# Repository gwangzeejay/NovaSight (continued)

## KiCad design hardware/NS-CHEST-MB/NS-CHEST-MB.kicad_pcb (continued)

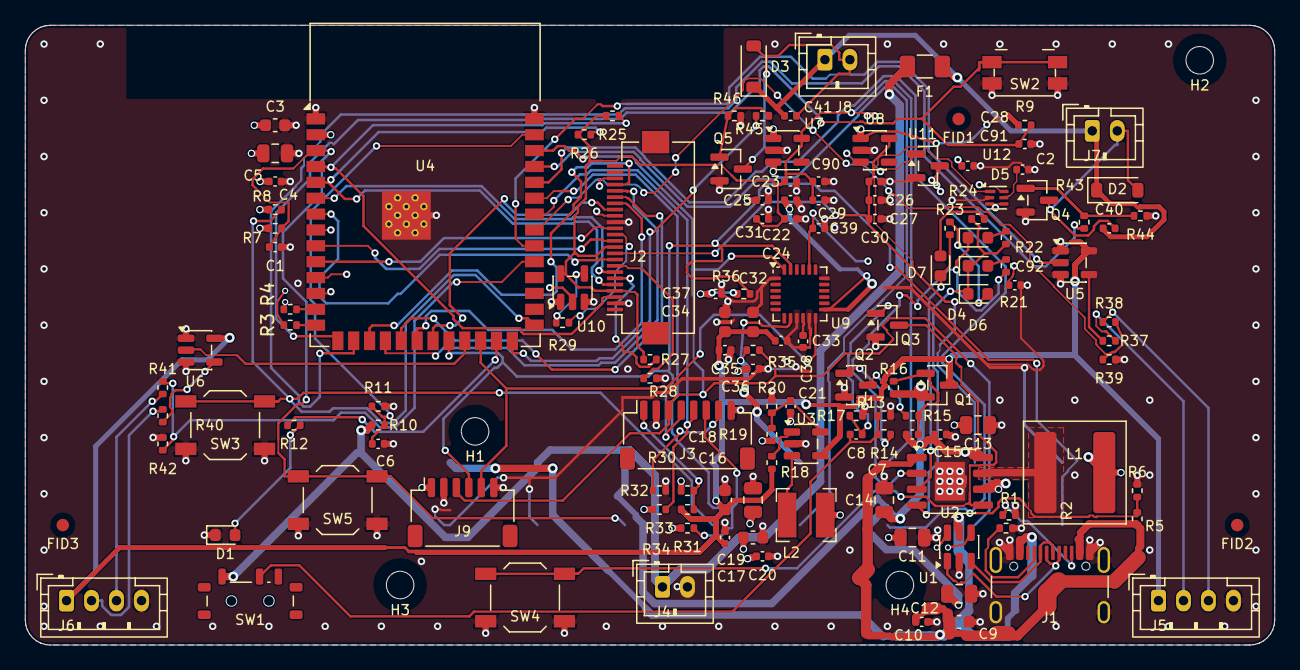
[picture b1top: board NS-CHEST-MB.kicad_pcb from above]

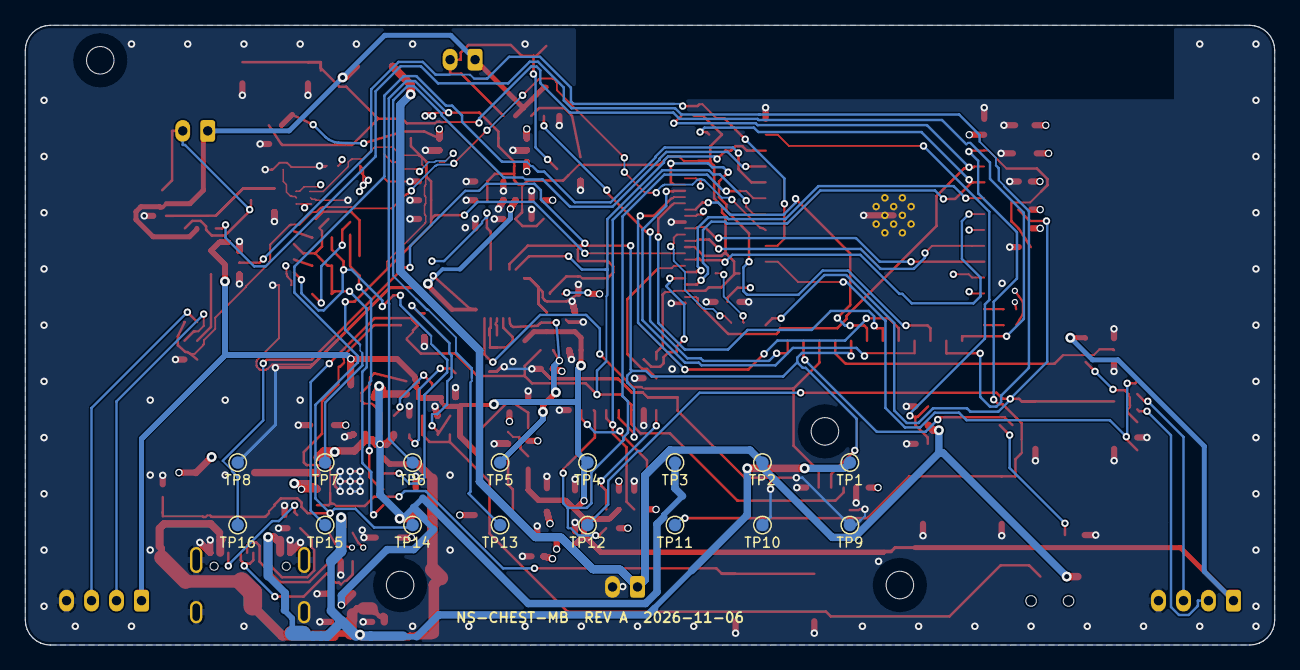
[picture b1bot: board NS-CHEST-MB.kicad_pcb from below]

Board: 4 copper layers, 100.0 x 49.6 mm, 154 parts (16 on the bottom side), 87 nets.

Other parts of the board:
FID1, FID2, FID3: FIDUCIAL; Fiducial_1mm_Mask2mm
H1, H2, H3, H4: M2_NPTH; MountingHole_2.2mm_M2

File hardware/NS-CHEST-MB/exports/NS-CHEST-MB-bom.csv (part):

"Refs","Value","Footprint","Qty","DNP"
"C1","1uF_10V","Capacitor_SMD:C_0402_1005Metric","1",""
"C2","100nF_10V","Capacitor_SMD:C_0402_1005Metric","1",""
"C3","10uF_10V","Capacitor_SMD:C_0603_1608Metric","1",""
"C4","100nF_10V","Capacitor_SMD:C_0402_1005Metric","1",""
"C5","22uF_10V","Capacitor_SMD:C_0805_2012Metric","1",""
"C6","100nF_10V","Capacitor_SMD:C_0402_1005Metric","1",""
"C7","100nF_10V","Capacitor_SMD:C_0402_1005Metric","1",""
"C8","1uF_10V","Capacitor_SMD:C_0402_1005Metric","1",""
"C9","10uF_10V","Capacitor_SMD:C_0603_1608Metric","1",""
"C10","100nF_10V","Capacitor_SMD:C_0402_1005Metric","1",""
"C11","22uF_10V","Capacitor_SMD:C_0805_2012Metric","1",""
"C12","22uF_10V","Capacitor_SMD:C_0805_2012Metric","1",""
"C13","22uF_10V","Capacitor_SMD:C_0805_2012Metric","1",""
"C14","22uF_10V","Capacitor_SMD:C_0805_2012Metric","1",""
"C15","100nF_10V","Capacitor_SMD:C_0402_1005Metric","1",""
"C16","10uF_10V","Capacitor_SMD:C_0603_1608Metric","1",""
"C17","100nF_10V","Capacitor_SMD:C_0402_1005Metric","1",""
"C18","22uF_10V","Capacitor_SMD:C_0805_2012Metric","1",""
"C19","10uF_10V","Capacitor_SMD:C_0603_1608Metric","1",""
"C20","100nF_10V","Capacitor_SMD:C_0402_1005Metric","1",""
"C21","22pF_50V","Capacitor_SMD:C_0402_1005Metric","1",""
"C22","1uF_10V","Capacitor_SMD:C_0402_1005Metric","1",""
"C23","1uF_10V","Capacitor_SMD:C_0402_1005Metric","1",""
"C24","100nF_10V","Capacitor_SMD:C_0402_1005Metric","1",""
"C25","1uF_10V","Capacitor_SMD:C_0402_1005Metric","1",""
"C26","1uF_10V","Capacitor_SMD:C_0402_1005Metric","1",""
"C27","100nF_10V","Capacitor_SMD:C_0402_1005Metric","1",""
"C28","100nF_10V","Capacitor_SMD:C_0402_1005Metric","1",""
"C29","1uF_10V","Capacitor_SMD:C_0402_1005Metric","1",""
"C30","1uF_10V","Capacitor_SMD:C_0402_1005Metric","1",""
"C31","1uF_10V","Capacitor_SMD:C_0402_1005Metric","1",""
"C32","10uF_10V","Capacitor_SMD:C_0603_1608Metric","1",""
"C33","100nF_10V","Capacitor_SMD:C_0402_1005Metric","1",""
"C34","10uF_10V","Capacitor_SMD:C_0603_1608Metric","1",""
"C35","100nF_10V","Capacitor_SMD:C_0402_1005Metric","1",""
"C36","100nF_10V","Capacitor_SMD:C_0402_1005Metric","1",""
"C37","10nF_10V","Capacitor_SMD:C_0402_1005Metric","1",""
"C38","100nF_10V","Capacitor_SMD:C_0402_1005Metric","1",""
"C39","2.2nF_50V","Capacitor_SMD:C_0402_1005Metric","1",""
"C40","100nF_10V","Capacitor_SMD:C_0402_1005Metric","1",""
"C41","100nF_10V","Capacitor_SMD:C_0402_1005Metric","1",""
"C90","100nF_10V","Capacitor_SMD:C_0402_1005Metric","1",""
"D1","STATUS_WHITE","LED_SMD:LED_0603_1608Metric","1",""
"D2","B5819W","Diode_SMD:D_SOD-123","1",""
"D3","B5819W","Diode_SMD:D_SOD-123","1",""
"D4","SOC_GREEN","LED_SMD:LED_0603_1608Metric","1",""
"D5","SOC_GREEN","LED_SMD:LED_0603_1608Metric","1",""
"D6","SOC_GREEN","LED_SMD:LED_0603_1608Metric","1",""
"D7","SOC_GREEN","LED_SMD:LED_0603_1608Metric","1",""
"F1","PTC_HOLD_0.5A","Fuse:Fuse_1206_3216Metric","1",""
"J1","USB-C","Connector_USB:USB_C_Receptacle_GCT_USB4105-xx-A_16P_TopMnt_Horizontal","1",""
"J2","OV5640_FPC_VERIFY_CONTACT","Connector_FFC-FPC:Hirose_FH12-24S-0.5SH_1x24-1MP_P0.50mm_Horizontal","1",""
"J3","TOF_HARNESS_VERIFY","Connector_JST:JST_SH_SM08B-SRSS-TB_1x08-1MP_P1.00mm_Horizontal","1",""
"J4","BATTERY_PROTECTED_1S","Connector_JST:JST_PH_B2B-PH-K_1x02_P2.00mm_Vertical","1",""
"J5","JSN_R_VERIFY","Connector_JST:JST_PH_B4B-PH-K_1x04_P2.00mm_Vertical","1",""
"J6","JSN_L_VERIFY","Connector_JST:JST_PH_B4B-PH-K_1x04_P2.00mm_Vertical","1",""
"J7","MOTOR_R","Connector_JST:JST_PH_B2B-PH-K_1x02_P2.00mm_Vertical","1",""
"J8","MOTOR_L","Connector_JST:JST_PH_B2B-PH-K_1x02_P2.00mm_Vertical","1",""
"J9","GY521_OPTION_DNP","Connector_JST:JST_SH_SM06B-SRSS-TB_1x06-1MP_P1.00mm_Horizontal","1","DNP"
"L1","XAL7020-102_1uH_VERIFY","Inductor_SMD:L_Coilcraft_XAL7020-102","1",""
"L2","2.2uH_Isat1.5A","Inductor_SMD:L_Bourns-SRN4018","1",""
"Q1","AO3401A","Package_TO_SOT_SMD:SOT-23","1",""
"Q2","AO3400A","Package_TO_SOT_SMD:SOT-23","1",""
"Q3","2N7002","Package_TO_SOT_SMD:SOT-23","1",""
"Q4","AO3400A","Package_TO_SOT_SMD:SOT-23","1",""
"Q5","AO3400A","Package_TO_SOT_SMD:SOT-23","1",""
"R1","5.1k_1%","Resistor_SMD:R_0402_1005Metric","1",""
"R2","5.1k_1%","Resistor_SMD:R_0402_1005Metric","1",""
"R3","0R","Resistor_SMD:R_0402_1005Metric","1",""
"R4","0R","Resistor_SMD:R_0402_1005Metric","1",""
"R5","68k_1%","Resistor_SMD:R_0402_1005Metric","1",""
"R6","100k_1%","Resistor_SMD:R_0402_1005Metric","1",""
"R7","10k","Resistor_SMD:R_0402_1005Metric","1",""
"R8","10k","Resistor_SMD:R_0402_1005Metric","1",""
"R9","10k","Resistor_SMD:R_0402_1005Metric","1",""
"R10","470k_1%","Resistor_SMD:R_0402_1005Metric","1",""
"R11","470k_1%","Resistor_SMD:R_0402_1005Metric","1",""
"R12","1k","Resistor_SMD:R_0402_1005Metric","1",""
"R13","100k","Resistor_SMD:R_0402_1005Metric","1",""
"R14","10k","Resistor_SMD:R_0402_1005Metric","1",""
"R15","10k","Resistor_SMD:R_0402_1005Metric","1",""
"R16","100k","Resistor_SMD:R_0402_1005Metric","1",""
"R17","470k","Resistor_SMD:R_0402_1005Metric","1",""
"R18","100k","Resistor_SMD:R_0402_1005Metric","1",""
"R19","680k_1%","Resistor_SMD:R_0402_1005Metric","1",""
"R20","150k_1%","Resistor_SMD:R_0402_1005Metric","1",""
"R21","1k","Resistor_SMD:R_0402_1005Metric","1",""
"R22","1k","Resistor_SMD:R_0402_1005Metric","1",""
"R23","1k","Resistor_SMD:R_0402_1005Metric","1",""
"R24","1k","Resistor_SMD:R_0402_1005Metric","1",""
"R25","4.7k","Resistor_SMD:R_0402_1005Metric","1",""
"R26","4.7k","Resistor_SMD:R_0402_1005Metric","1",""
"R27","10k","Resistor_SMD:R_0402_1005Metric","1",""
"R28","10k","Resistor_SMD:R_0402_1005Metric","1",""
"R29","22R","Resistor_SMD:R_0402_1005Metric","1",""
"R30","0R","Resistor_SMD:R_0402_1005Metric","1",""
"R31","0R_OPTION_5V","Resistor_SMD:R_0402_1005Metric","1","DNP"
"R32","0R","Resistor_SMD:R_0402_1005Metric","1",""
"R33","47k","Resistor_SMD:R_0402_1005Metric","1",""
"R34","47k","Resistor_SMD:R_0402_1005Metric","1","DNP"
"R35","2.2k","Resistor_SMD:R_0402_1005Metric","1",""
"R36","2.2k","Resistor_SMD:R_0402_1005Metric","1",""
"R37","100R","Resistor_SMD:R_0402_1005Metric","1",""
"R38","10k_1%","Resistor_SMD:R_0402_1005Metric","1",""
"R39","15k_1%","Resistor_SMD:R_0402_1005Metric","1",""
"R40","100R","Resistor_SMD:R_0402_1005Metric","1",""
"R41","10k_1%","Resistor_SMD:R_0402_1005Metric","1",""
"R42","15k_1%","Resistor_SMD:R_0402_1005Metric","1",""
"R43","100R","Resistor_SMD:R_0402_1005Metric","1",""
"R44","100k","Resistor_SMD:R_0402_1005Metric","1",""
"R45","100R","Resistor_SMD:R_0402_1005Metric","1",""
"R46","100k","Resistor_SMD:R_0402_1005Metric","1",""
"SW1","POWER_ON","Button_Switch_SMD:SW_SPDT_Shouhan_MSK12C02","1",""
"SW2","MODE_EVQPUJ02K_SIDE","Button_Switch_SMD:Panasonic_EVQPUJ_EVQPUA","1",""
"SW3","BOOT","Button_Switch_SMD:SW_SPST_TL3342","1",""
"SW4","IP_KEY_TEST","Button_Switch_SMD:SW_SPST_TL3342","1","DNP"
"SW5","RESET","Button_Switch_SMD:SW_SPST_TL3342","1",""
"TP1","VBUS","TestPoint:TestPoint_Pad_D1.0mm","1",""
"TP2","VBAT","TestPoint:TestPoint_Pad_D1.0mm","1",""
"TP3","5V_SYS","TestPoint:TestPoint_Pad_D1.0mm","1",""
"TP4","5V_SW","TestPoint:TestPoint_Pad_D1.0mm","1",""
"TP5","3V3","TestPoint:TestPoint_Pad_D1.0mm","1",""
"TP6","2V8","TestPoint:TestPoint_Pad_D1.0mm","1",""
"TP7","1V5","TestPoint:TestPoint_Pad_D1.0mm","1",""
"TP8","GND","TestPoint:TestPoint_Pad_D1.0mm","1",""
"TP9","GND","TestPoint:TestPoint_Pad_D1.0mm","1",""
"TP10","GND","TestPoint:TestPoint_Pad_D1.0mm","1",""
"TP11","MCU_EN","TestPoint:TestPoint_Pad_D1.0mm","1",""
"TP12","BOOT","TestPoint:TestPoint_Pad_D1.0mm","1",""
"TP13","UART_TX","TestPoint:TestPoint_Pad_D1.0mm","1",""
"TP14","VBUS_DET","TestPoint:TestPoint_Pad_D1.0mm","1",""
"TP15","I2C_SDA","TestPoint:TestPoint_Pad_D1.0mm","1",""
"TP16","I2C_SCL","TestPoint:TestPoint_Pad_D1.0mm","1",""
"U1","USBLC6-2SC6","Package_TO_SOT_SMD:SOT-23-6","1",""
"U2","IP5306","Package_SO:HSOP-8-1EP_3.9x4.9mm_P1.27mm_EP2.41x3.1mm","1",""
"U3","SY8088IAAC","Package_TO_SOT_SMD:SOT-23-5","1",""
"U4","ESP32-S3-WROOM-1-N16R8","RF_Module:ESP32-S3-WROOM-1","1",""
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
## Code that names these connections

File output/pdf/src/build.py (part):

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    boxes = {'usb': (0, 0, 'J1 USB-C', 'VBUS 4,65–5,5 V', True), 'ip': (1, 0, 'U2 IP5306', 'Sạc 2,1 A + boost 5 V', False),
             'q1': (2, 0, 'Q1 AO3401A', 'Công tắc tải 5V_SYS → 5V_SW', False), 'buck': (3, 0, 'U3 SY8088IAAC', 'Buck 3,3 V, tối đa 1 A', False),
             'v33': (4, 0, '3V3', 'ESP32-S3, MPU-6050, ToF', True),
             'bat': (1, 1, 'J4 pin LP124065', 'VBAT 3,0–4,2 V (có mạch bảo vệ)', True), 'sw': (2, 1, 'SW1 → Q2', 'PWR_EN kéo gate Q1 xuống', False),
             'jsn': (3, 1, 'U5, U6 + J5, J6', '5V_SW: 2 JSN-SR04T, buffer TRIG', False), 'ldo': (4, 1, 'U7 2V8 · U8 1V5', 'Camera AVDD/DOVDD · DVDD', False),
             'f1': (1, 2, 'F1 PTC 0,5 A', 'VBAT → VBAT_MOT', False), 'mot': (2, 2, 'Q4, Q5 + J7, J8', 'Low-side AO3400A, 2 motor 1027', False)}
    arrows = [('line', 'usb', 'r', 'ip', 'l'), ('line', 'ip', 'r', 'q1', 'l'), ('line', 'q1', 'r', 'buck', 'l'), ('line', 'buck', 'r', 'v33', 'l'),
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    # elbow from battery bottom down to Q2 right side: custom since it leaves from bottom
    arrows = [a for a in arrows if a[0] != 'elbow']
    _tree('NovaCane Clip Cây nguồn', 'Mạch chia tải cho phép máy chạy khi cắm sạc; motor lấy nguồn từ VSYS.', boxes, arrows,
          'Khi có VBUS, gate Q2 lên 5 V nên Q2 ngắt; VSYS lấy từ USB qua D4 và TP4056 sạc pin đúng dòng đặt. GND trên bo là P− của mạch bảo vệ; B− không được nối GND ở chỗ khác.')
    # pin → Q2 (battery bottom to Q2 right)
    bxp = 64 + 3 * 238 + 95; yq = H - 135 - 118 - 35
    c.setStrokeColor(GRAY); c.setLineWidth(1.2); c.line(bxp, H - 135 - 70, bxp, yq)
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def block_chest():
    doc.std('NovaChest Kiến trúc phần cứng', 'Mọi GPIO của ESP32-S3 đã được dùng hết; GPIO35–37 bị PSRAM octal chiếm.', 1)
    cx, cy, cw, chh = 400, H - 130, 280, 330
    doc.box(cx, cy, cw, chh, 'U4 ESP32-S3-WROOM-1-N16R8', 'Wi-Fi/BLE 5, 16 MB flash, 8 MB PSRAM\nI²C 400 kHz (GPIO2/14)\nUSB nội GPIO19/20', fill=HEAD, stroke=RED, tsize=15, bsize=12)
    L = [('J1 USB-C + U1 USBLC6', 'CC 5,1 kΩ ×2, D+/D−, VBUS_DET GPIO44'), ('SW2 Mode · SW3 BOOT · SW5 RESET', 'GPIO3, GPIO0, EN'),
         ('U9 MPU-6050', 'I²C 0x68, INT GPIO47'), ('J3 ToF VL53L8CX', 'I²C 0x29, LPn GPIO41, INT GPIO42'), ('Đo pin', 'VBAT/2 → GPIO1 (ADC1_CH0)')]
    R = [('J2 camera FPC 24 chân', 'DVP 8 bit, SCCB GPIO4/5, XCLK GPIO15'), ('U5, U6 → J5, J6 JSN-SR04T', 'TRIG GPIO21/39, ECHO GPIO38/40'),
         ('Q4, Q5 → J7, J8 motor', 'PWM GPIO45/46, kéo xuống 100 kΩ'), ('D1 LED trạng thái', 'GPIO48'), ('TP1–TP16', 'Test point các rail và tín hiệu')]
    for i, (t, b) in enumerate(L):
        yt = H - 125 - i * 66
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
def block_clip():
    doc.std('NovaCane Clip Kiến trúc phần cứng', 'ESP32-C3-MINI-1: một cổng USB-Serial-JTAG dùng cho cả sạc và nạp firmware.', 1)
    doc.box(400, H - 130, 280, 330, 'U1 ESP32-C3-MINI-1-N4X', 'BLE 5, I²C GPIO4/5\nUSB D− GPIO18, D+ GPIO19\nBOOT GPIO9, strapping GPIO2/8/9', fill=HEAD, stroke=RED, tsize=15, bsize=12)
    L = [('J1 USB-C + U2 USBLC6', 'VBUS_DET GPIO21 (cầu chia 68 kΩ / 100 kΩ)'), ('SW2 Mode · SW3 Xin đường · SW4 SOS', 'GPIO10, GPIO2, GPIO20'),
         ('U6 MPU-6050', 'I²C 0x68, INT GPIO1'), ('Đo pin', 'BAT+/2 → GPIO0 (ADC1_CH0)'), ('SW1 công tắc gạt', 'EN của U4 (LDO) nối VSYS khi ON')]
    R = [('Q3, Q4 → motor trái/phải', 'PWM GPIO6/7, VSYS, flyback B5819W'), ('Q5 → D1, D2, D3', 'GPIO3, 2 Hz, 3 nhánh có điện trở riêng'),
         ('D9 LED trạng thái', 'GPIO8, sáng khi mức thấp'), ('D7, D8 CHRG/STDBY', 'Chỉ để kỹ thuật viên xem khi mở vỏ'), ('TP1–TP13', 'Test point các rail và tín hiệu')]
    for i, (t, b) in enumerate(L):
        yt = H - 125 - i * 66
        doc.box(64, yt, 280, 56, t, b, tsize=13, bsize=11); doc.arrow(344, yt - 28, 400, yt - 28)
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rows = [['Khối', 'Linh kiện', 'Hoạt động'],
        ['Sạc', 'U3 TP4056 (ESOP-8), R_PROG 3,0 kΩ', 'I = 1200 / 3,0 = 400 mA; TEMP nối GND; CE nối VCC; pad đáy nối GND'],
        ['Bảo vệ pin', 'U5 DW01A + Q1 FS8205A', '100 Ω từ B+ vào VCC, 100 nF VCC–B−, 1 kΩ từ CS đến P−; FS8205A nằm trên đường B− → P−'],
        ['Chia tải', 'D4 SS14 + Q2 AO3401A', 'Không cắm sạc: gate = 0 V, Q2 dẫn, pin cấp VSYS. Cắm sạc: gate = 5 V, Q2 ngắt, VSYS lấy từ USB qua D4'],
        ['LDO', 'U4 AP2112K-3.3', 'VIN = VSYS; EN nối VSYS qua SW1; ra 10 µF + 100 nF, thêm 22 µF sát chân 3V3 của module'],
        ['Công tắc', 'SW1', 'Chỉ mang dòng µA; OFF thì LDO tắt, dòng còn lại ≈ 4,5 µA cầu chia pin + dòng nghỉ DW01A']]
y_cs = doc.table(64, H - 115, [130, 270, 536], rows, size=15, pad=6.5)
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
S = lambda x0, y0, x1, y1: (x0 / 2000, y0 / 1413, x1 / 2000, y1 / 1413)
sch_page('NovaChest schematic MCU, boot và giao diện', 'Phần 1: ESP32-S3, EN/BOOT, nút Mode, LED trạng thái và đo pin.', 'CH', S(29, 80, 665, 560),
         'U4 ESP32-S3-WROOM-1-N16R8.\nEN: 10 kΩ lên 3V3, 1 µF xuống GND, nút RESET (SW5).\nGPIO0: 10 kΩ lên 3V3, nút BOOT (SW3).\nSW2 Mode: GPIO3, 10 kΩ lên 3V3, 100 nF.\nD1 LED trạng thái: GPIO48 → 1 kΩ.\nĐo pin: VBAT → 470 kΩ / 470 kΩ → GPIO1, 100 nF.')
sch_page('NovaChest schematic nguồn, sạc và bảo vệ', 'Phần 2: IP5306, công tắc tải Q1/Q2/Q3, buck SY8088 và 4 LED báo pin.', 'CH', S(670, 100, 1440, 600),
         'U2 IP5306: VIN = VBUS, BAT = VBAT, SW → L1 → BAT, VOUT = 5V_SYS.\nQ1 AO3401A là công tắc tải 5V_SYS → 5V_SW; Q2 AO3400A và Q3 2N7002 tạo xung KEY.\nU3 SY8088IAAC: R trên 680 kΩ, R dưới 150 kΩ, feed-forward 22 pF cho 3,32 V.\nD4–D7 là mạch báo pin 4 LED.')
sch_page('NovaChest schematic USB-C, ESD và VBUS', 'Phần 3: J1 USB-C, USBLC6-2SC6, CC1/CC2 và cầu chia VBUS_DET.', 'CH', S(29, 590, 665, 1010),
         'CC1 và CC2 mỗi chân một điện trở 5,1 kΩ 1% xuống GND (thiết bị sink).\nD+ nối GPIO20, D− nối GPIO19, có footprint 0 Ω nối tiếp.\nU1 USBLC6-2SC6 bảo vệ D+/D− và VBUS.\nVBUS → 68 kΩ / 100 kΩ → GPIO44 (VBUS_DET), 2,98 V ở 5,0 V.')
sch_page('NovaChest schematic IMU, I²C và cảm biến ngoài', 'Phần 4: MPU-6050, connector ToF và hai connector JSN-SR04T.', 'CH', S(670, 610, 1440, 1100),
         'U9 MPU-6050: VDD 3V3 + 100 nF, VLOGIC 3V3 + 10 nF, REGOUT 100 nF, CPOUT 2,2 nF.\nAD0, CLKIN, FSYNC nối GND; INT nối GPIO47.\nJ3 ToF: VIN_TOF qua JP1 (0 Ω).\nJ5/J6: 5V_SW, TRIG qua buffer 74AHCT1G125, ECHO qua cầu chia 10 kΩ + 15 kΩ.')
sch_page('NovaChest schematic camera và các rail phụ', 'Phần 7: FPC camera, ME6211 2V8/1V5 và buffer XCLK.', 'CH', S(1440, 48, 1960, 640),
         'J2 FPC 24 chân: pinout theo thiết kế tham chiếu ESP32-S3-EYE.\nU7 ME6211C28M5G-N cấp 2V8 (AVDD, DOVDD); U8 ME6211C15M5G-N cấp 1V5 (DVDD).\nSCCB kéo lên 2V8 bằng 4,7 kΩ; RESET 10 kΩ lên 2V8; PWDN 10 kΩ xuống GND.')
sch_page('NovaChest schematic motor và đèn', 'Phần 5: Q4/Q5, diode flyback, PTC F1 và hai connector motor.', 'CH', S(1440, 640, 1990, 1010),
         'J7/J8 chân 1 = VBAT_MOT sau PTC F1 (0,5 A), chân 2 = MOT−.\nQ4/Q5 AO3400A là khóa phía thấp, gate qua 100 Ω và kéo xuống 100 kΩ.\nGate motor trái nối GPIO45, phải nối GPIO46; 100 kΩ giữ hai chân strapping ở mức 0 lúc khởi động.\nD2/D3 B5819W flyback; 100 nF tại connector.')

# GPIO table
doc.std('NovaChest bảng gán chân ESP32-S3', 'Chân module lấy theo symbol ESP32-S3-WROOM-1; GPIO35–37 (chân 28–30) bị PSRAM octal chiếm.', 2)
gp = [('0', '27', 'BOOT', 'Strapping, 10 kΩ lên, SW3'), ('1', '39', 'VBAT_ADC', 'ADC1_CH0'), ('2', '38', 'I2C_SDA', 'Cảm biến'),
      ('3', '15', 'BTN_MODE', 'Strapping JTAG, kéo lên'), ('4', '4', 'CAM_SIOD', 'SCCB'), ('5', '5', 'CAM_SIOC', 'SCCB'),
      ('6', '6', 'CAM_VSYNC', ''), ('7', '7', 'CAM_HREF', ''), ('8', '12', 'CAM_Y4', ''), ('9', '17', 'CAM_Y3', ''),
      ('10', '18', 'CAM_Y5', ''), ('11', '19', 'CAM_Y2', ''), ('12', '20', 'CAM_Y6', ''), ('13', '21', 'CAM_PCLK', ''),
      ('14', '22', 'I2C_SCL', 'Cảm biến'), ('15', '8', 'CAM_XCLK', 'Qua R 22 Ω'), ('16', '9', 'CAM_Y9', ''),
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      ('21', '23', 'JSN_L_TRIG', 'Qua U6'), ('38', '31', 'JSN_L_ECHO', 'Qua cầu chia'), ('39', '32', 'JSN_R_TRIG', 'Qua U5'),
      ('40', '33', 'JSN_R_ECHO', 'Qua cầu chia'), ('41', '34', 'TOF_LPN', '47 kΩ lên'), ('42', '35', 'TOF_INT', ''),
      ('43', '37', 'TXD0', 'Chỉ test point'), ('44', '36', 'VBUS_DET', 'Cầu chia 68k/100k'),
      ('45', '26', 'MOT_L_PWM', 'Strapping = 0, 100 kΩ xuống'), ('46', '16', 'MOT_R_PWM', 'Strapping = 0, 100 kΩ xuống'),
      ('47', '24', 'IMU_INT', ''), ('48', '25', 'LED_STATUS', '')]
# verify against design json pins
u4pins = [x for x in DES['chest'] if x['ref'] == 'U4'][0]['pins']
mism = [(g, p, f) for g, p, f, _ in gp if (u4pins.get(p) or '').replace('_SRC', '').replace('_IN', '') not in (f, f.replace('BTN_MODE', 'BTN_MODE'))]
half = (len(gp) + 1) // 2
hdr = ['GPIO', 'Chân', 'Tín hiệu', 'Ghi chú']
doc.table(40, H - 120, [48, 48, 128, 255], [hdr] + [list(r) for r in gp[:half]], size=11, pad=4.5, mono=(0, 1, 2))
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doc.text(710, H - 120, 300, 'TP4056 và DW01A + FS8205A đặt gần pad pin B+/B−. Pad đáy TP4056 cần nối mảng đồng ≥ 100 mm².\n\nGND trên bo là P− của mạch bảo vệ; B− chỉ nối qua FS8205A.', 14, INK)

sch_page('NovaCane Clip schematic MCU, boot và nút', 'Phần 1: ESP32-C3-MINI-1, EN/BOOT, ba nút, LED trạng thái và đo pin.', 'CL', S(29, 80, 665, 560),
         'U1 ESP32-C3-MINI-1-N4X: 3V3 10 µF + 100 nF; EN 10 kΩ lên 3V3 + 1 µF.\nGPIO9 (BOOT), GPIO8 và GPIO2 đều kéo lên 10 kΩ.\nSW2 Mode GPIO10, SW3 Xin đường GPIO2, SW4 SOS GPIO20; mỗi nút 10 kΩ lên 3V3 và 100 nF.\nĐo pin: BAT+ → 470 kΩ / 470 kΩ → GPIO0.')
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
